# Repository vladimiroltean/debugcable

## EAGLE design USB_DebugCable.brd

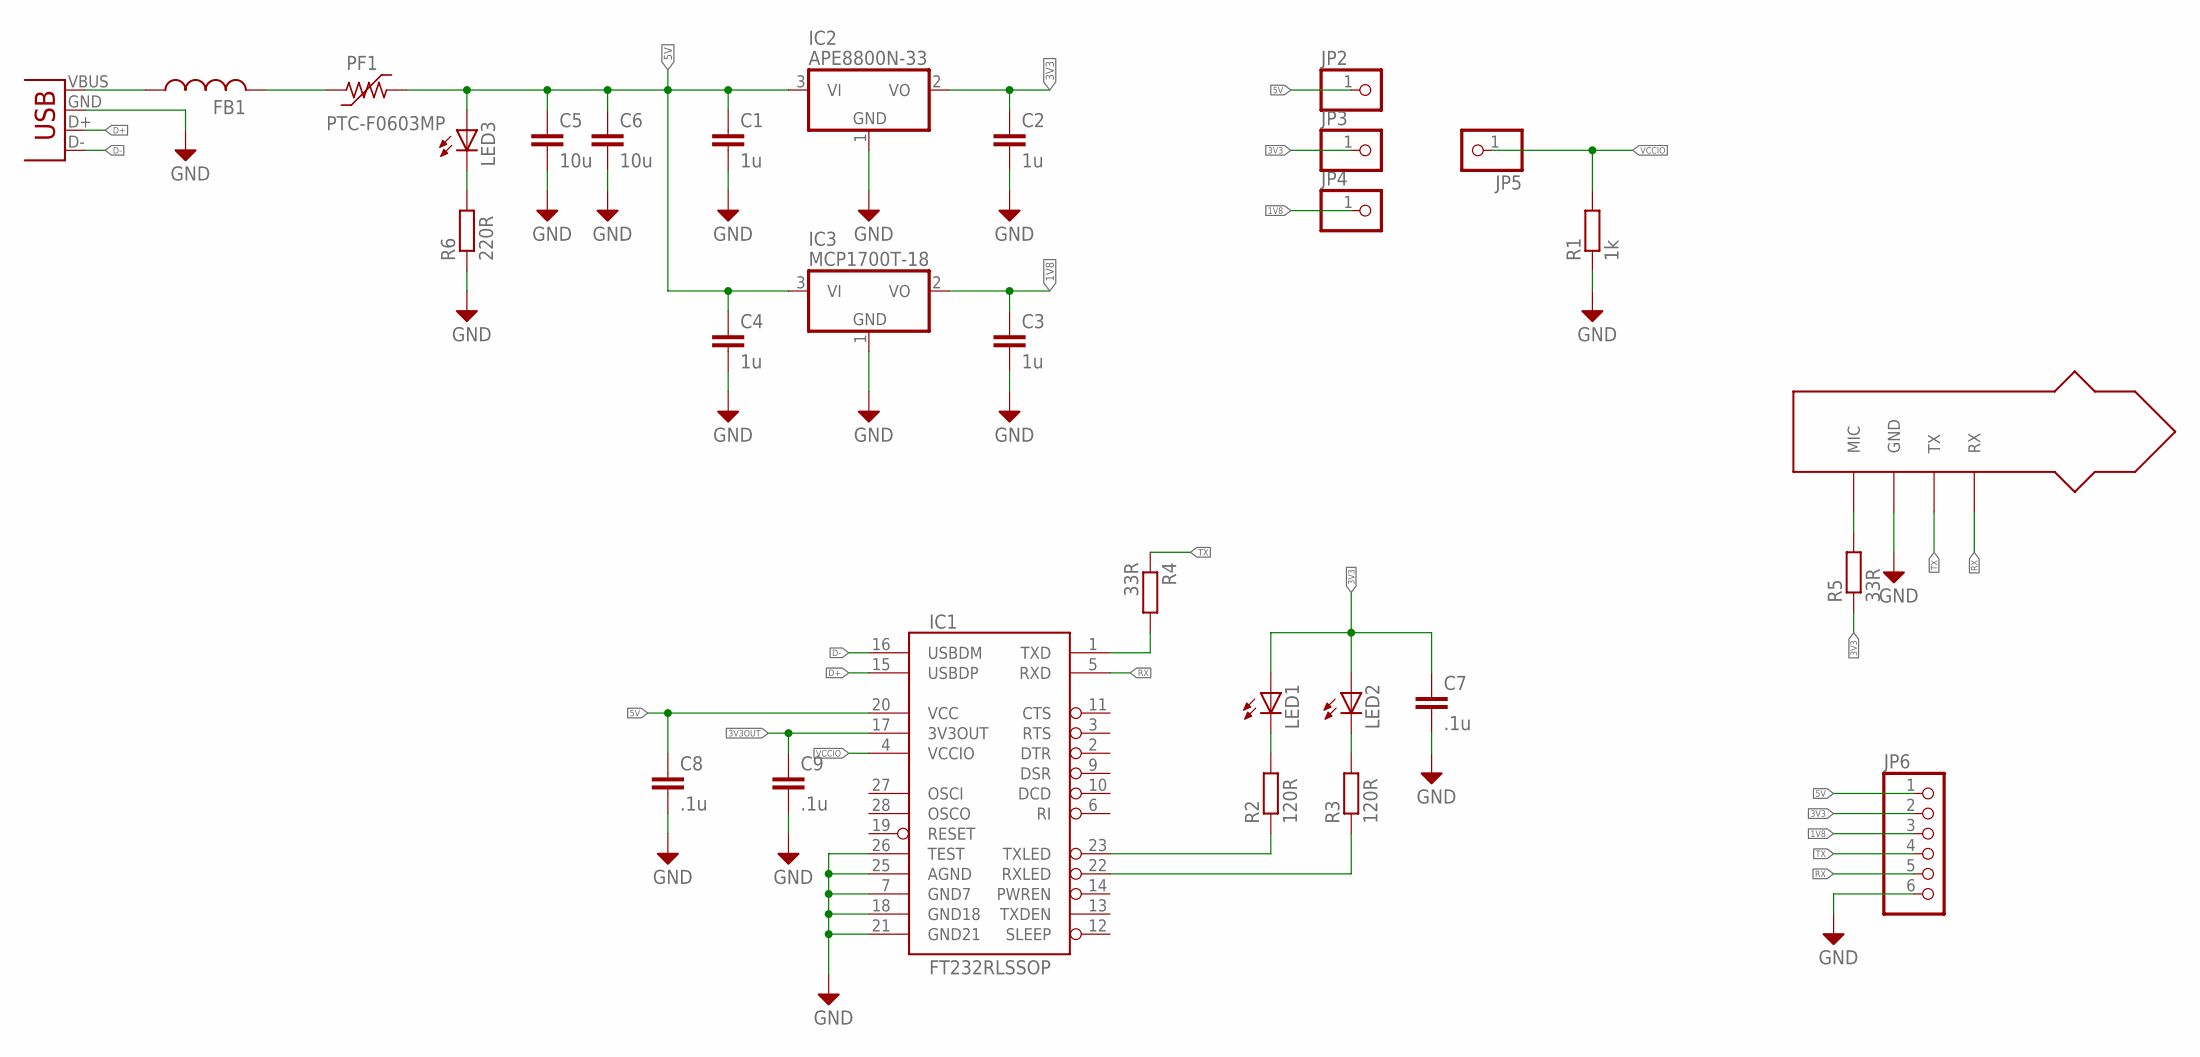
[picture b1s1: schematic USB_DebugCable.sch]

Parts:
C1, C2, C3, C4: 1u; C0603K
C5, C6: 10u; C0603K
C7: .1u; C0603K
C8, C9: .1u; C0402K
FB1: FERRITE-BEADA; 0603
IC1: FT232RLSSOP; SSOP28DB
IC2: APE8800N-33; SOT23
IC3: MCP1700T-18; SOT23
JP1: USB-A-H
JP2, JP3, JP4, JP5: PINHD-1X1; 1X01
JP6: PINHD-1X6CB; 1X06-CLEANBIG
LED1, LED2, LED3: LEDCHIPLED_0603; CHIPLED_0603
PF1: PTC-F0603MP; F0603MP
R1: 1k; R0603
R2, R3: 120R; R0603
R4, R5: 33R; R0603
R6: 220R; R0603
U$1: JACK3.5_4; 3.5MM4

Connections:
1V8: C3.1, IC3.2 (VO), JP4.1, JP6.3
3V3: C2.1, C7.1, IC2.2 (VO), JP3.1, JP6.2, LED1.A, LED2.A, R5.1
3V3OUT: C9.1, IC1.17 (3V3OUT)
5V: C1.1, C4.1, C5.1, C6.1, C8.1, IC1.20 (VCC), IC2.3 (VI), IC3.3 (VI), JP2.1, JP6.1, LED3.A, PF1.2
D+: IC1.15 (USBDP), JP1.D+ (D-)
D-: IC1.16 (USBDM), JP1.D- (D+)
GND: C1.2, C2.2, C3.2, C4.2, C5.2, C6.2, C7.2, C8.2, C9.2, IC1.7 (GND7), IC1.18 (GND18), IC1.21 (GND21), IC1.25 (AGND), IC1.26 (TEST), IC2.1 (GND), IC3.1 (GND), JP1.GND (VBUS), JP6.6, R1.1, R6.1, U$1.GND
unnamed: FB1.1, JP1.VBUS (GND)
unnamed: R5.2, U$1.MIC_1 (MIC), U$1.MIC_2 (MIC)
unnamed: IC1.1 (TXD), R4.2
unnamed: FB1.2, PF1.1
unnamed: IC1.23 (TXLED), R2.1
unnamed: IC1.22 (RXLED), R3.1
unnamed: LED1.C, R2.2
unnamed: LED2.C, R3.2
unnamed: LED3.C, R6.2
RX: IC1.5 (RXD), JP6.5, U$1.RX_1 (RX), U$1.RX_2 (RX)
TX: JP6.4, R4.1, U$1.TX
VCCIO: IC1.4 (VCCIO), JP5.1, R1.2

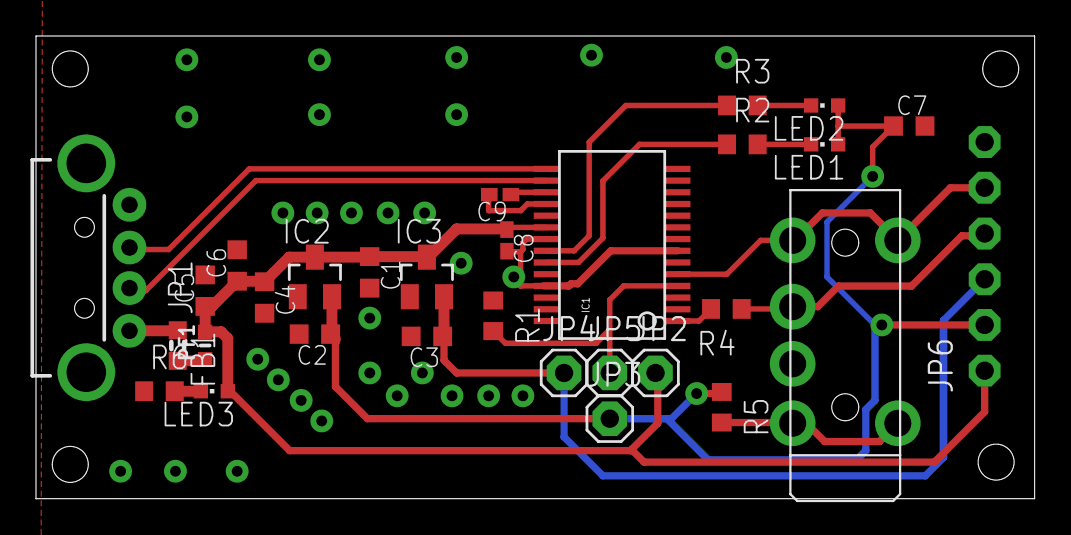
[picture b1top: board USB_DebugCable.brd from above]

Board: 2 copper layers, 55.5 x 25.7 mm, 30 parts (0 on the bottom side), 19 nets.

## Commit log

2015-05-06 Initial empty repository
2015-05-06 USB debug cable design documents
    Eagle schematics and PCB, gerber files, and BOM for a debug cable
    for the headset serial port found on most Nexus devices.
2016-11-11 ape8800n: initial version
2016-11-11 fc68128: initial commit, first version
2016-11-22 Schematic, board and library updates

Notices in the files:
parts and their libraries:
SparkFun-Connectors: Licensing: CC v3.0 Share-Alike You are welcome to use this library for commercial purposes.
polyswitch: Copyright (C) 2008, Bob Starr
m-pad-2.1: License : GNU General Public License version 2 (see bottom)
